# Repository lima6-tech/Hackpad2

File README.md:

# Hackpad2
Revised hackpad submission. A custom hackpad/macropad featuring 4 mechanical key switches, a rotary encoder with a push-button function, an acrylic & 3D-printed sandwich enclosure, and KMK firmware running on CircuitPython.

PCB design

*Note that if these images are still broken, these are the same images as the ones in Assets*

---

## Features

* **Microcontroller:** Seeed Studio XIAO.
* **Inputs:** 4 direct-wired MX mechanical key switches + 1 rotary encoder with integrated push switch.
* **Firmware:** [KMK Firmware](https://github.com/KMKFW/kmk_firmware) on CircuitPython for drag-and-drop keymap edits.
* **CAD:** Sandwich design consisting of a 3D-printed top cover, main base, column and a laser-cut acrylic "window" Assembled using M3 standoffs and machine screws.
*Note: the "column" is not attached to the top because it is 3D printed - it will be attached separately*
* **PCB:** Designed in Kicad (Also see PCB above):

Schematics

CAD design

---

## Keymaps
  * **Encoder:** Rotate for Previous/Next Track; Press for Play/Pause.
  * **SW1, SW2, SW3:** Undo (`Ctrl+Z`), Copy (`Ctrl+C`), Paste (`Ctrl+V`).
  * I might later add multiple key command layers.

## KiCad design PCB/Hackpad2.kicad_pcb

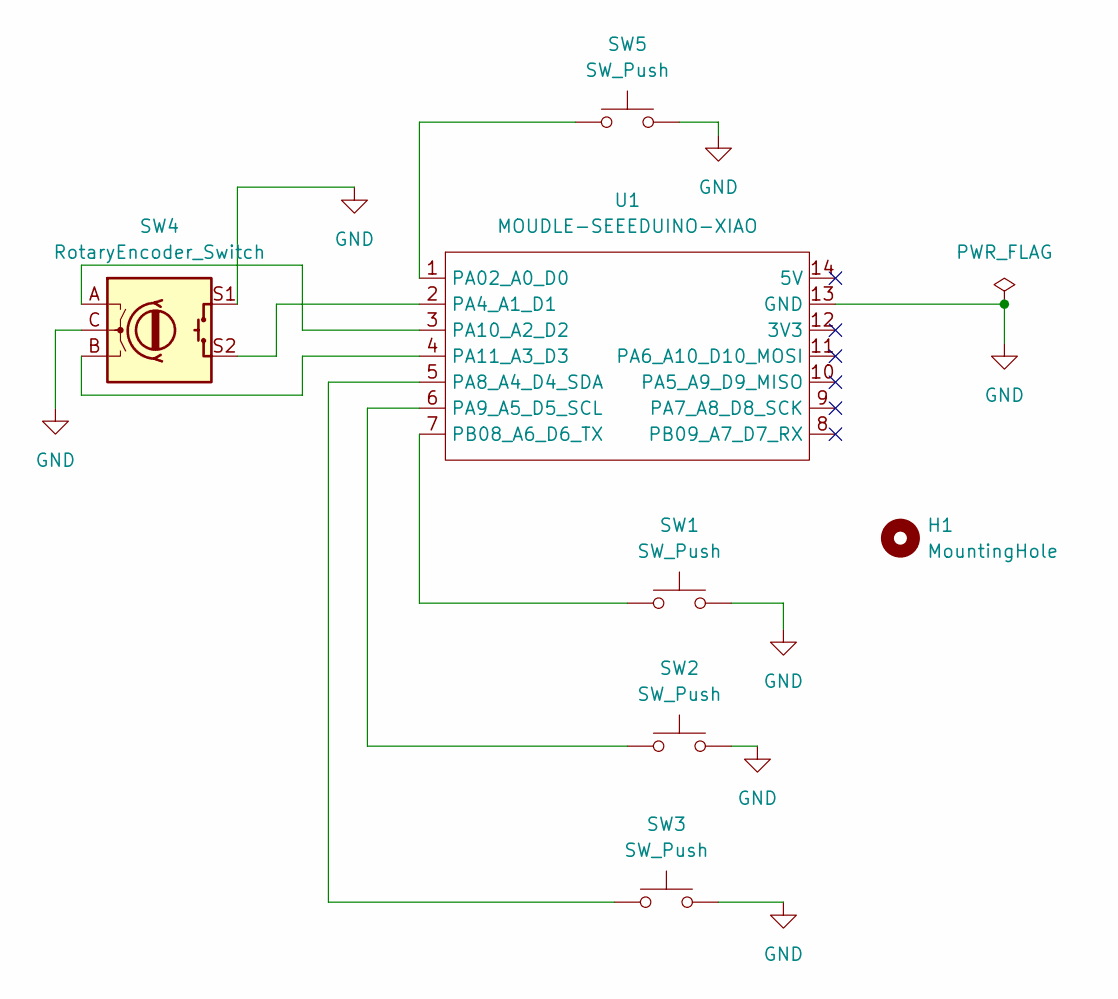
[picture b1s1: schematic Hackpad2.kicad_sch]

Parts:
H1: MountingHole; MountingHole_3.2mm_M3
SW1, SW2, SW3, SW5: SW_Push; SW_Cherry_MX_1.00u_PCB
SW4: RotaryEncoder_Switch; RotaryEncoder_Alps_EC11E-Switch_Vertical_H20mm
U1: MOUDLE-SEEEDUINO-XIAO; XIAO-Generic-Hybrid-14P-2.54-21X17.8MM

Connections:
GND: SW1.2, SW2.2, SW3.2, SW4.C, SW4.S1, SW5.2, U1.13 (GND)
unnamed: SW5.1, U1.1 (PA02_A0_D0)
unnamed: SW4.S2, U1.2 (PA4_A1_D1)
unnamed: SW3.1, U1.5 (PA8_A4_D4_SDA)
unnamed: SW2.1, U1.6 (PA9_A5_D5_SCL)
unnamed: SW4.A, U1.3 (PA10_A2_D2)
unnamed: SW4.B, U1.4 (PA11_A3_D3)
unnamed: SW1.1, U1.7 (PB08_A6_D6_TX)

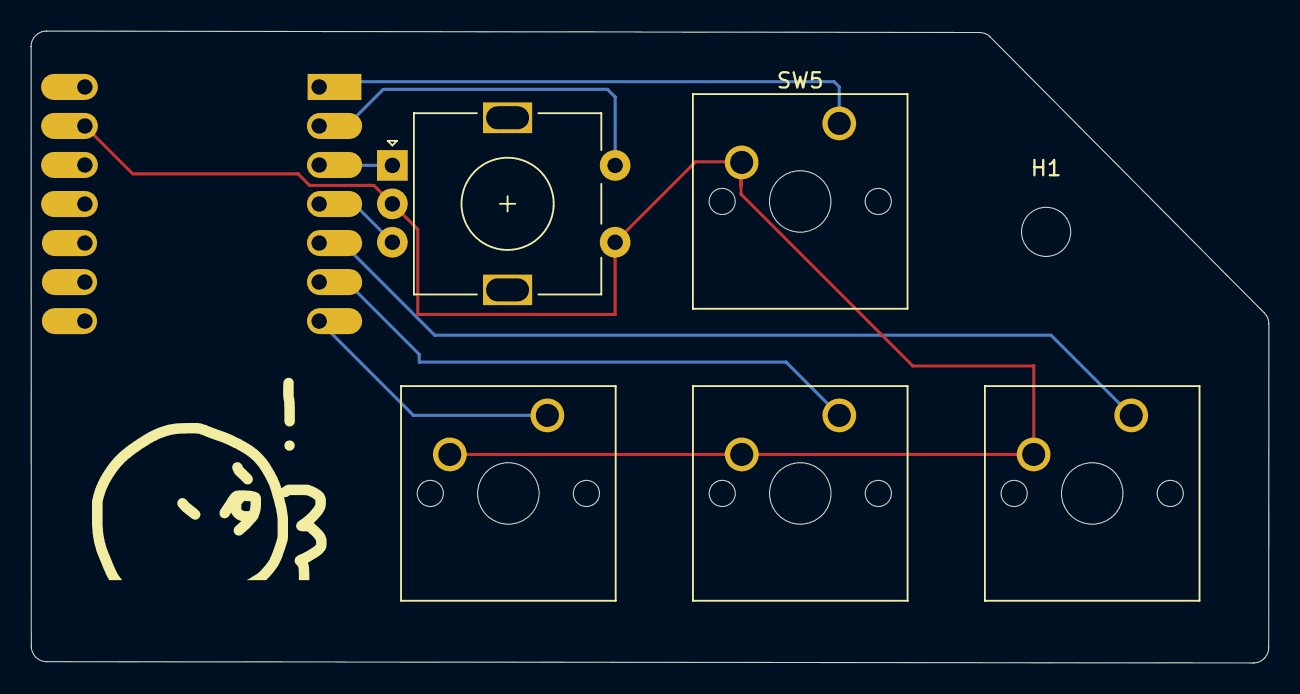
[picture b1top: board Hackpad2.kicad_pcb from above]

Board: 2 copper layers, 80.6 x 41.1 mm, 7 parts (1 on the bottom side), 8 nets.
